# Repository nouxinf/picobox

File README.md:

# picobox
tiny raspberry pi pico games console!

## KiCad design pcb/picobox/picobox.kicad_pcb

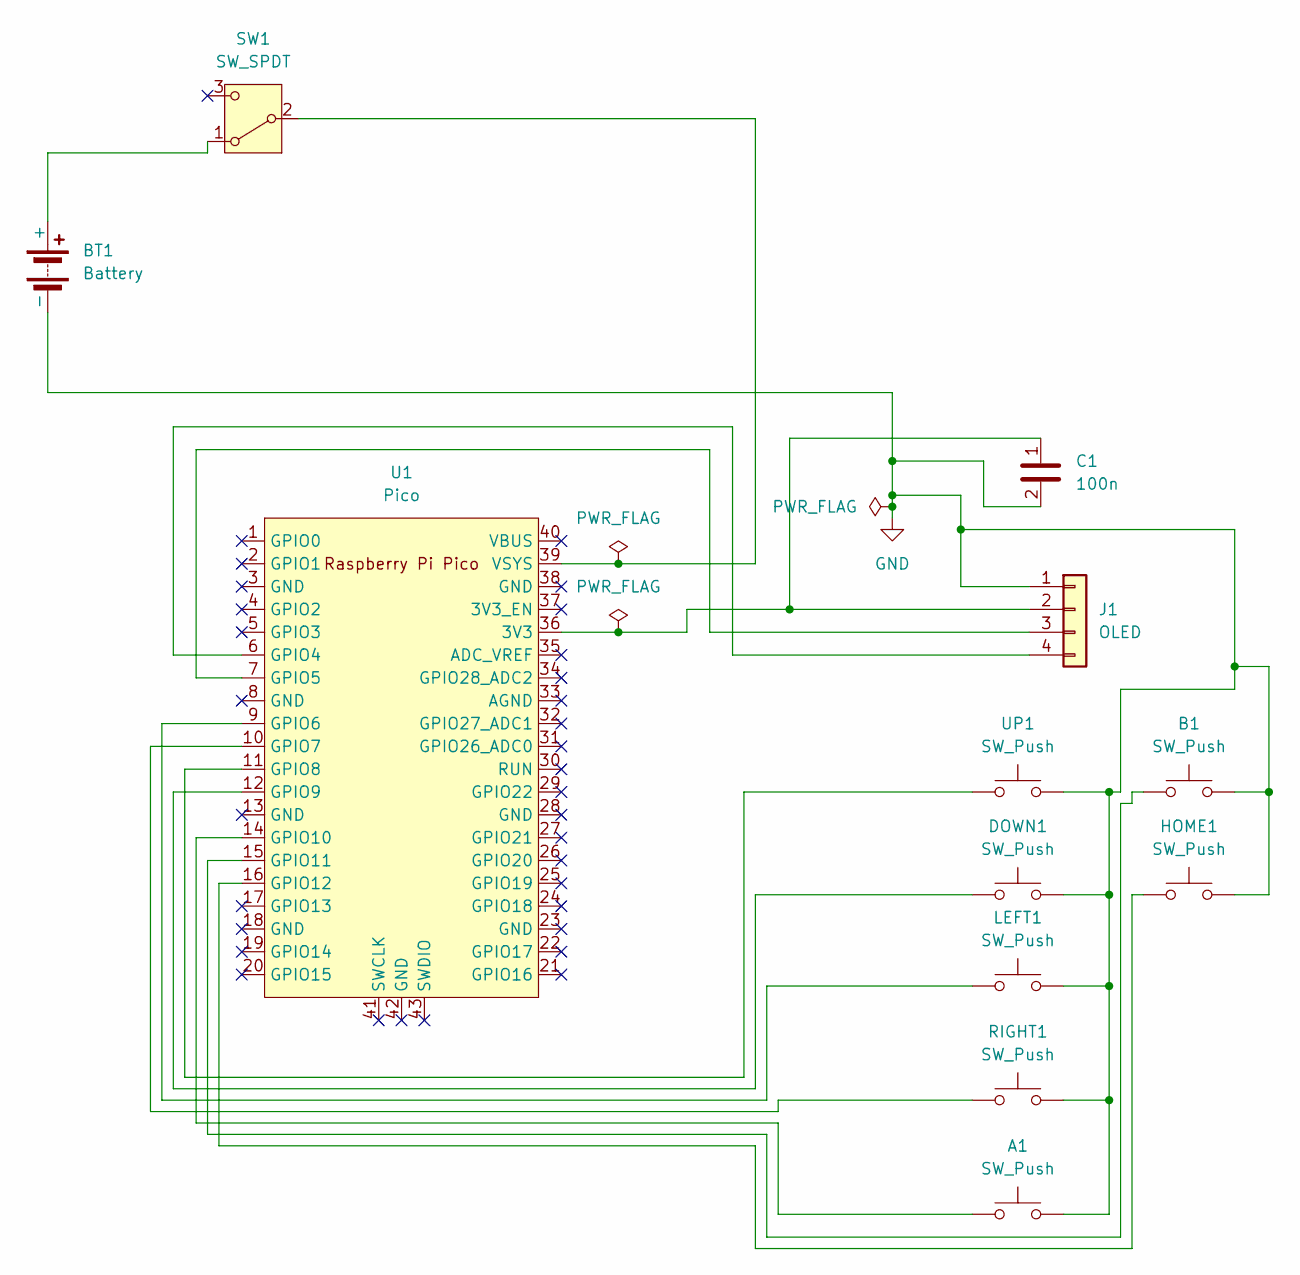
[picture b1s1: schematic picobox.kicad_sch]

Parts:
A1: SW_Push; SW_PUSH_6mm
B1: SW_Push; SW_PUSH_6mm
BT1: Battery; BatteryHolder_Keystone_2462_2xAA
C1: 100n; C_Disc_D5.0mm_W2.5mm_P5.00mm
DOWN1: SW_Push; SW_PUSH_6mm
HOME1: SW_Push; SW_PUSH_6mm
J1: OLED; PinHeader_1x04_P2.54mm_Horizontal
LEFT1: SW_Push; SW_PUSH_6mm
RIGHT1: SW_Push; SW_PUSH_6mm
SW1: SW_SPDT; SW_Slide_SPDT_Straight_CK_OS102011MS2Q
U1: Pico; RPi_Pico_SMD_TH
UP1: SW_Push; SW_PUSH_6mm

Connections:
GND: A1.2, B1.2, BT1.2 (-), C1.2, DOWN1.2, HOME1.2, J1.1, LEFT1.2, RIGHT1.2, UP1.2
unnamed: BT1.1 (+), SW1.1 (A)
unnamed: C1.1, J1.2, U1.36 (3V3)
unnamed: J1.3, U1.7 (GPIO5)
unnamed: J1.4, U1.6 (GPIO4)
unnamed: SW1.2 (B), U1.39 (VSYS)
unnamed: LEFT1.1, U1.9 (GPIO6)
unnamed: RIGHT1.1, U1.10 (GPIO7)
unnamed: U1.11 (GPIO8), UP1.1
unnamed: DOWN1.1, U1.12 (GPIO9)
unnamed: A1.1, U1.14 (GPIO10)
unnamed: B1.1, U1.15 (GPIO11)
unnamed: HOME1.1, U1.16 (GPIO12)

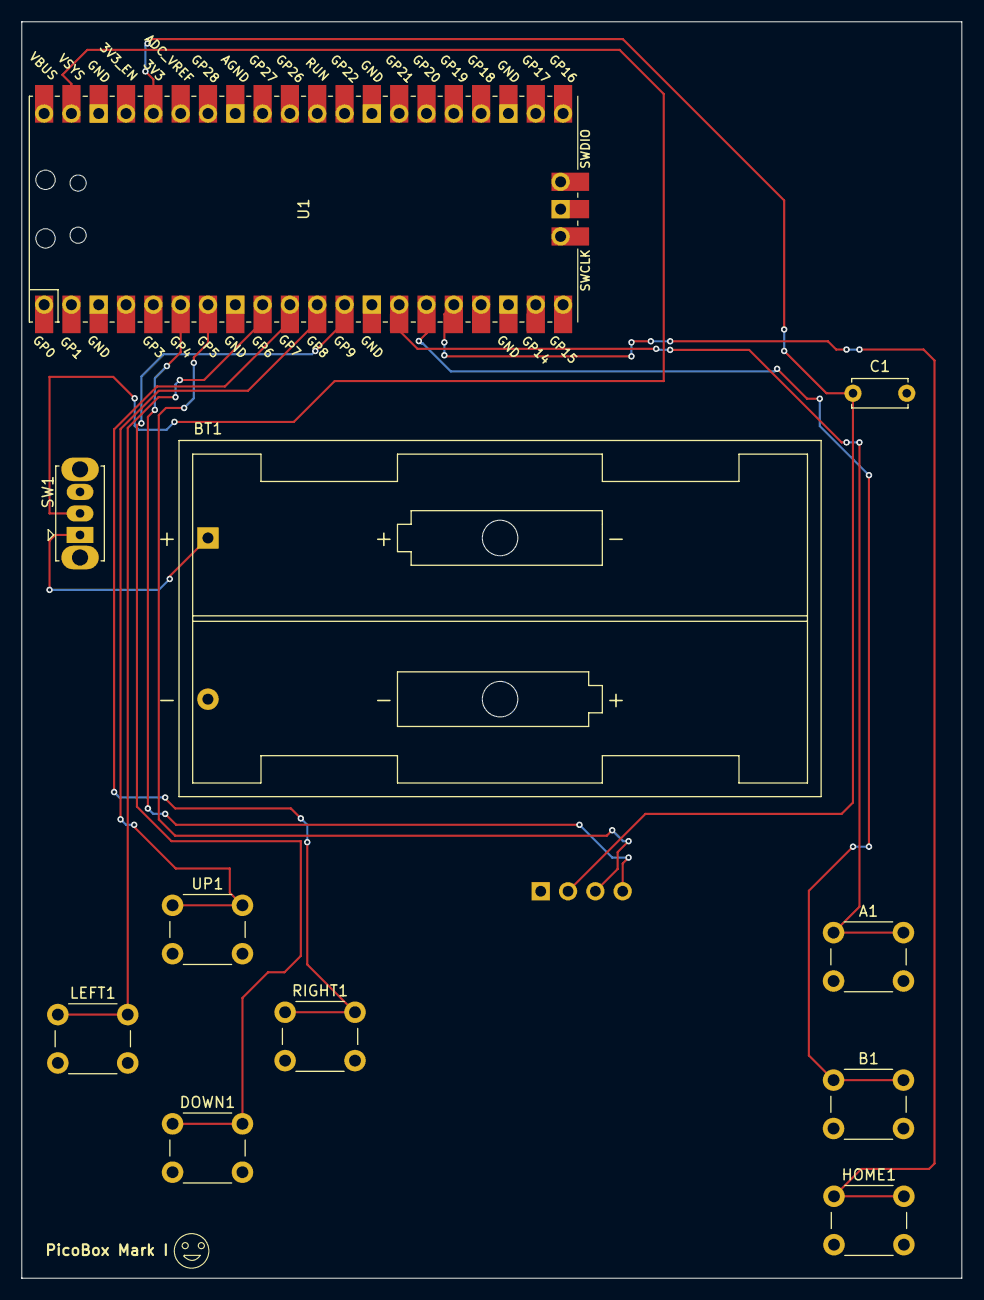
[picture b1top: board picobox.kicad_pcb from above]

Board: 2 copper layers, 87.4 x 116.8 mm, 12 parts (1 on the bottom side), 13 nets.
